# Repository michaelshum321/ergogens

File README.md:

# Ergogen stuff

## [sofle-clone (but it's actually bad)] (sofle-clone/README.md)
My first time playing with ergogen! and my first time in the DIY Keeb space :)

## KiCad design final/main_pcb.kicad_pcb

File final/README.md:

Things changed here:
* made very right edge cut slightly more to the right to account for 0.3mm gap as defined by JLCPCB
* made connecting top right edge stretch slightly more to reach new right edge position
* same with the other side of the right edge

Things did:
Front: horizontal traces
Back: vertical traces

Except for the MCU, which was a bit of a cluster fuck

Change TRRS Power to RAW since it needs to power the other board. oops!

GNDs between the two MCU footpirnts couldn't connect under the footprint, so GND at the top left had to reach around to do it. oops!

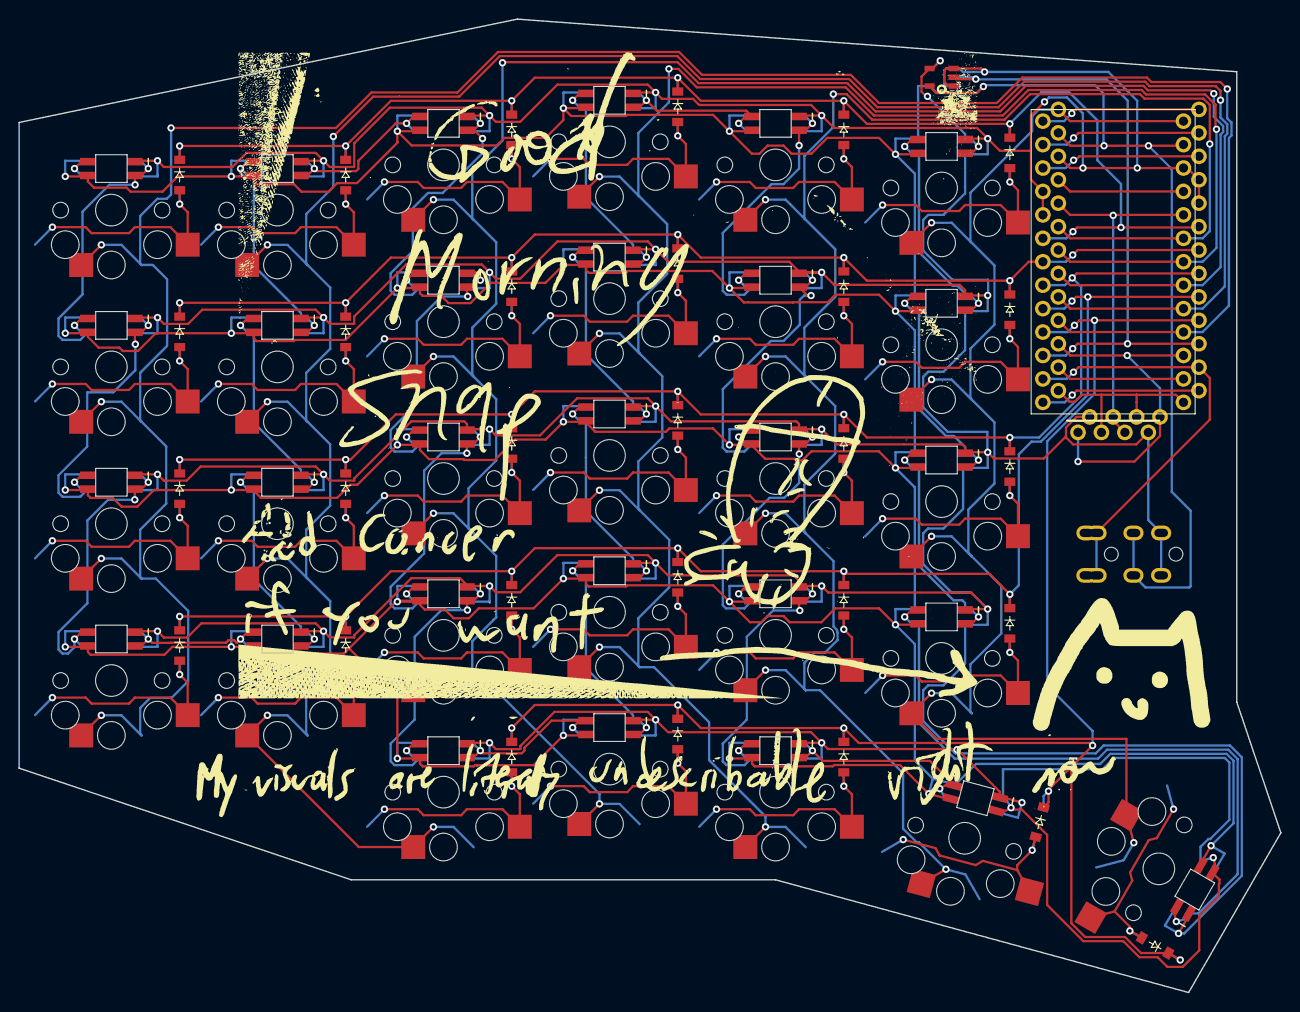
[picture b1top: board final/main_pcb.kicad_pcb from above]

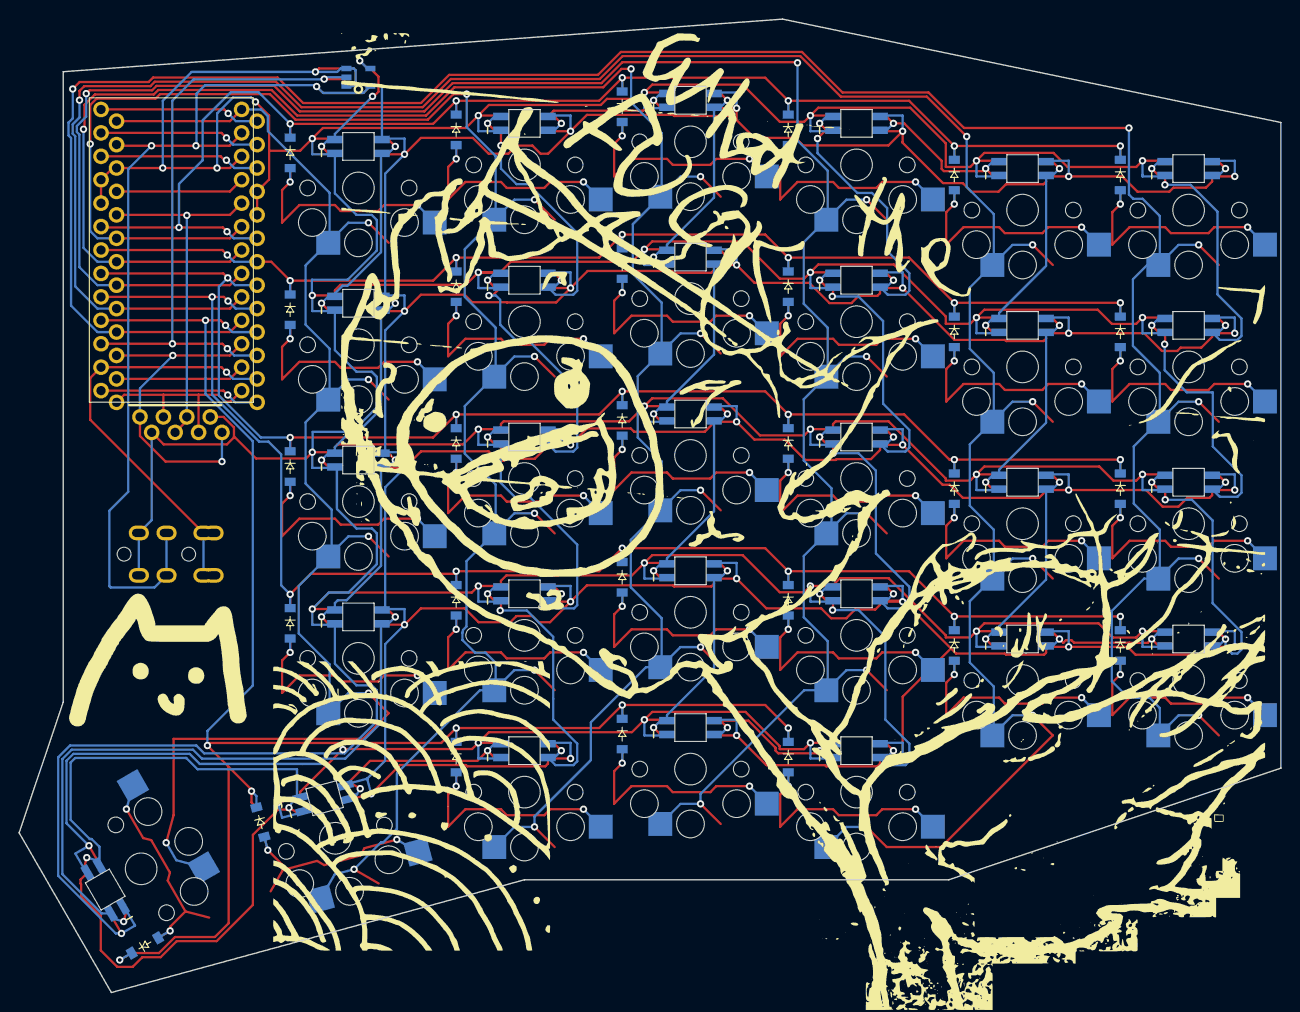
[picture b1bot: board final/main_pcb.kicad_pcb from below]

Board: 2 copper layers, 136.8 x 105.5 mm, 94 parts (31 on the bottom side), 82 nets.

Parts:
 : LOGO; plantjohnny_100
D1, D2, D3, D4, D5, D6, D7, D8, D9, D10, D11, D12, D13, D14, D15, D16, D17, D18, D19, D20, D21, D22, D23, D24, D25, D26, D27, D28, D29: ComboDiode
MCU-AX1, MCU-AX2: ProMicroAX
OLED1, OLED2: OLED
S1, S2, S3, S4, S5, S6, S7, S8, S9, S10, S11, S12, S13, S14, S15, S16, S17, S18, S19, S20, S21, S22, S23, S24, S25, S26, S27, S28, S29: PG1350
TRRS1: TRRS-PJ-320A-dual
_1, _2, _3, _4, _5, _6, _7, _8, _9, _10, _11, _12, _13, _14, _15, _16, _17, _18, _19, _20, _21, _22, _23, _24, _25, _26, _27, _28, _29: SK6812-MINI-E; sk6812-mini-e
_30: 74AHCT1G125

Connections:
3V3: MCU-AX1.VDD, MCU-AX2.VDD, OLED1.VCC, OLED2.VCC
CIndex: MCU-AX1.P29, MCU-AX2.P29, S20.1, S21.1, S22.1, S23.1, S28.1
CInner: MCU-AX1.P11, MCU-AX2.P11, S24.1, S25.1, S26.1, S27.1, S29.1
CMid: MCU-AX1.P28, MCU-AX2.P28, S15.1, S16.1, S17.1, S18.1, S19.1
COuter: MCU-AX1.P22, MCU-AX2.P22, S1.1, S2.1, S3.1, S4.1
CPinky: MCU-AX1.P26, MCU-AX2.P26, S5.1, S6.1, S7.1, S8.1, S9.1
CRing: MCU-AX1.P27, MCU-AX2.P27, S10.1, S11.1, S12.1, S13.1, S14.1
GND: MCU-AX1.GND, MCU-AX2.GND, OLED1.GND, OLED2.GND, TRRS1.4, _1.GND, _2.GND, _3.GND, _4.GND, _5.GND, _6.GND, _7.GND, _8.GND, _9.GND, _10.GND, _11.GND, _12.GND, _13.GND, _14.GND, _15.GND, _16.GND, _17.GND, _18.GND, _19.GND, _20.GND, _21.GND, _22.GND, _23.GND, _24.GND, _25.GND, _26.GND, _27.GND, _28.GND, _29.GND, _30.GND
LED_1: _26.DIN, _27.DOUT
LED_2: _25.DIN, _26.DOUT
LED_3: _24.DIN, _25.DOUT
LED_4: _24.DOUT, _29.DIN
LED_5: _28.DIN, _29.DOUT
LED_6: _19.DIN, _28.DOUT
LED_7: _19.DOUT, _20.DIN
LED_8: _20.DOUT, _21.DIN
LED_9: _21.DOUT, _22.DIN
LED_10: _22.DOUT, _23.DIN
LED_11: _18.DIN, _23.DOUT
LED_12: _17.DIN, _18.DOUT
LED_13: _16.DIN, _17.DOUT
LED_14: _15.DIN, _16.DOUT
LED_15: _14.DIN, _15.DOUT
LED_16: _9.DIN, _14.DOUT
LED_17: _9.DOUT, _10.DIN
LED_18: _10.DOUT, _11.DIN
LED_19: _11.DOUT, _12.DIN
LED_20: _12.DOUT, _13.DIN
LED_21: _8.DIN, _13.DOUT
LED_22: _7.DIN, _8.DOUT
LED_23: _6.DIN, _7.DOUT
LED_24: _5.DIN, _6.DOUT
LED_25: _1.DIN, _5.DOUT
LED_26: _1.DOUT, _2.DIN
LED_27: _2.DOUT, _3.DIN
LED_28: _3.DOUT, _4.DIN
LED_START_3V3: MCU-AX1.P7, MCU-AX2.P7, _30.DIN
LED_START_5V: _27.DIN, _30.DOUT
OLED_SCL: MCU-AX1.P21, MCU-AX2.P21, OLED1.SCL, OLED2.SCL
OLED_SDA: MCU-AX1.P20, MCU-AX2.P20, OLED1.SDA, OLED2.SDA
P0: MCU-AX1.P0, MCU-AX2.P0
P1: MCU-AX1.P1, MCU-AX2.P1
P9: MCU-AX1.P9, MCU-AX2.P9
P10: MCU-AX1.P10, MCU-AX2.P10
P23: MCU-AX1.P23, MCU-AX2.P23
RAW: MCU-AX1.RAW, MCU-AX2.RAW, TRRS1.3, _1.VDD, _2.VDD, _3.VDD, _4.VDD, _5.VDD, _6.VDD, _7.VDD, _8.VDD, _9.VDD, _10.VDD, _11.VDD, _12.VDD, _13.VDD, _14.VDD, _15.VDD, _16.VDD, _17.VDD, _18.VDD, _19.VDD, _20.VDD, _21.VDD, _22.VDD, _23.VDD, _24.VDD, _25.VDD, _26.VDD, _27.VDD, _28.VDD, _29.VDD, _30.VCC
RBottom: D1.2, D5.2, D10.2, D15.2, D20.2, D24.2, MCU-AX1.P5, MCU-AX2.P5
RHome: D2.2, D6.2, D11.2, D16.2, D21.2, D25.2, MCU-AX1.P4, MCU-AX2.P4
RMod: D9.2, D14.2, D19.2, D28.2, D29.2, MCU-AX1.P6, MCU-AX2.P6
RNum: D4.2, D8.2, D13.2, D18.2, D23.2, D27.2, MCU-AX1.P2, MCU-AX2.P2
RST: MCU-AX1.RST, MCU-AX2.RST
RTop: D3.2, D7.2, D12.2, D17.2, D22.2, D26.2, MCU-AX1.P3, MCU-AX2.P3
TRS_DATA: MCU-AX1.P8, MCU-AX2.P8, TRRS1.1, TRRS1.2
index_bottom: D20.1, S20.2
index_home: D21.1, S21.2
index_mod: D19.1, S19.2
index_num: D23.1, S23.2
index_top: D22.1, S22.2
inner_bottom: D24.1, S24.2
inner_home: D25.1, S25.2
inner_num: D27.1, S27.2
inner_top: D26.1, S26.2
layer_cluster: D28.1, S28.2
middle_bottom: D15.1, S15.2
middle_home: D16.1, S16.2
middle_mod: D14.1, S14.2
middle_num: D18.1, S18.2
middle_top: D17.1, S17.2
outer_bottom: D1.1, S1.2
outer_home: D2.1, S2.2
outer_num: D4.1, S4.2
outer_top: D3.1, S3.2
pinky_bottom: D5.1, S5.2
pinky_home: D6.1, S6.2
pinky_num: D8.1, S8.2
pinky_top: D7.1, S7.2
ring_bottom: D10.1, S10.2
ring_home: D11.1, S11.2
ring_mod: D9.1, S9.2
ring_num: D13.1, S13.2
ring_top: D12.1, S12.2
space_cluster: D29.1, S29.2

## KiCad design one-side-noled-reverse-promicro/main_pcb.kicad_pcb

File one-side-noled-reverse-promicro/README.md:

The Pro Micros are wired up so that the two footprints are all connected on the Front, except for 1 via closest to one side's pin.

This way, there is more space to have vias in the middle of the ProMicro for other important things

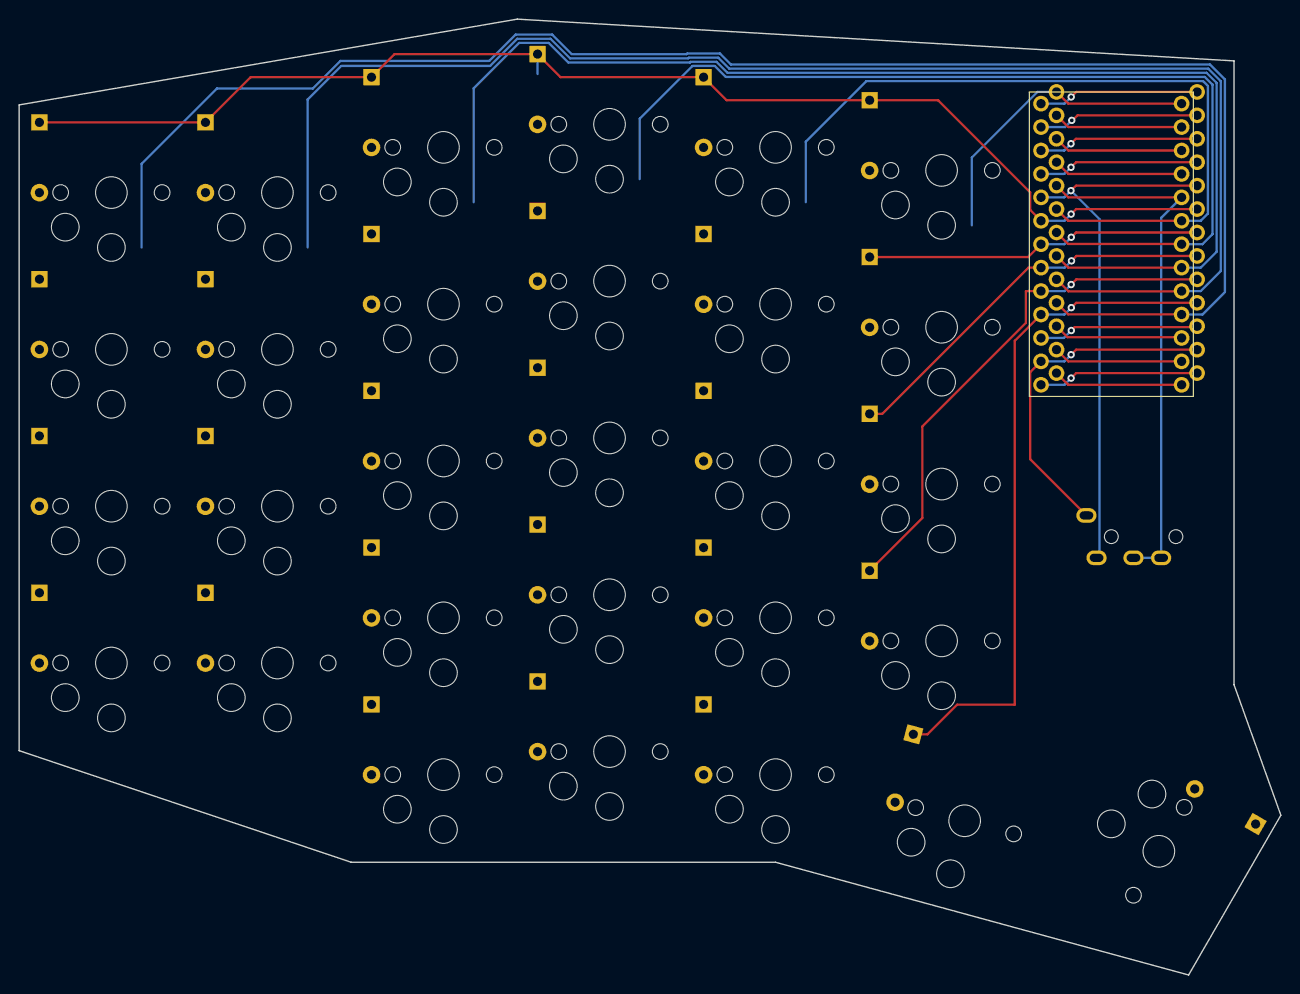
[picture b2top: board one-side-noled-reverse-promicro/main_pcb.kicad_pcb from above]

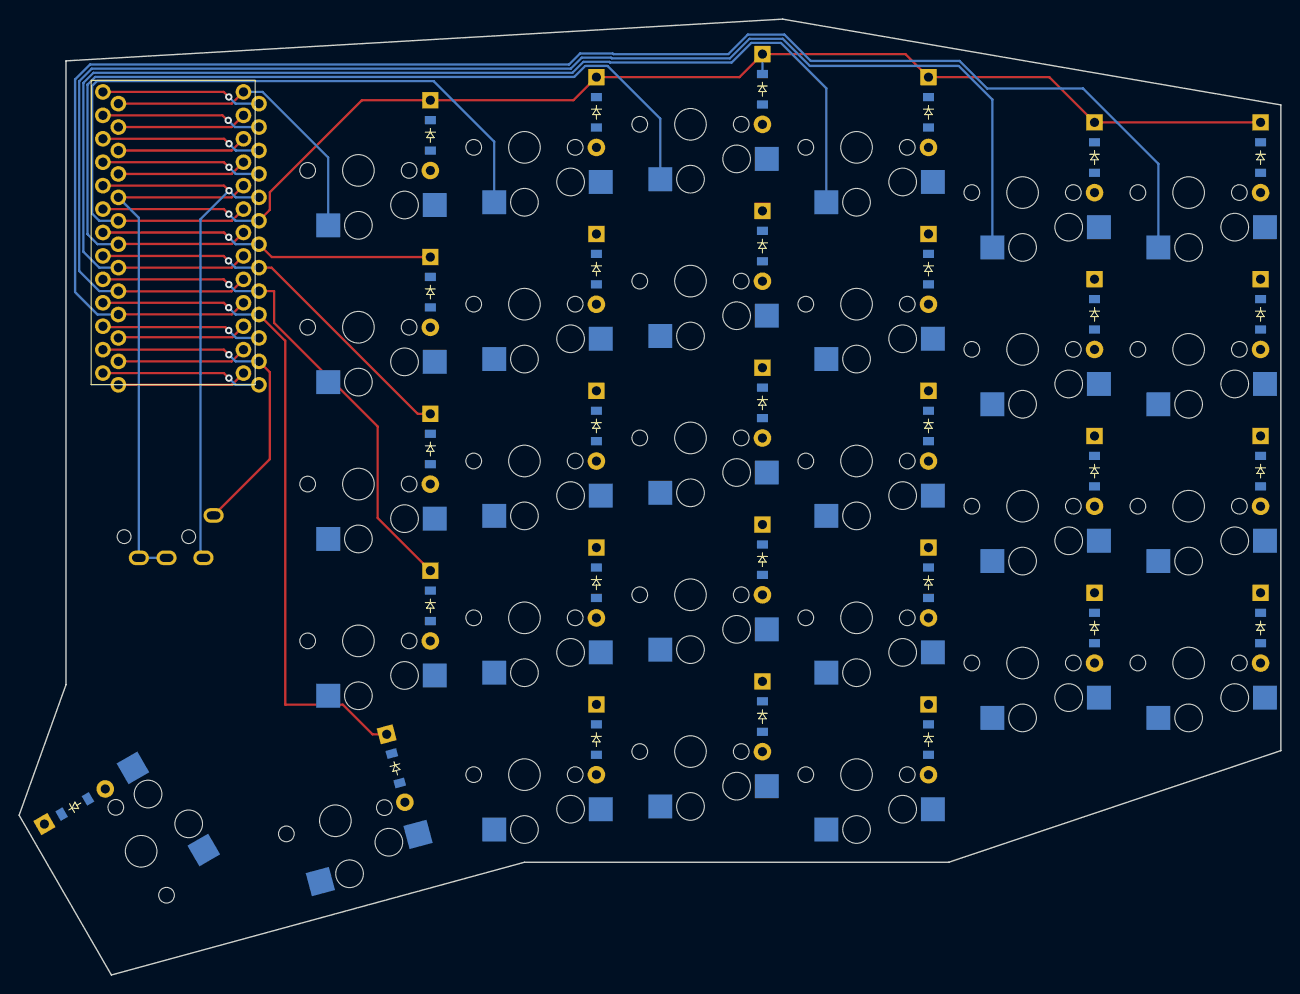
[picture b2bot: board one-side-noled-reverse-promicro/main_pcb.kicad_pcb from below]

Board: 2 copper layers, 136.8 x 103.6 mm, 61 parts (30 on the bottom side), 53 nets.

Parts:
D1, D2, D3, D4, D5, D6, D7, D8, D9, D10, D11, D12, D13, D14, D15, D16, D17, D18, D19, D20, D21, D22, D23, D24, D25, D26, D27, D28, D29: ComboDiode
MCU-AX1, MCU-AX2: ProMicroAX
S1, S2, S3, S4, S5, S6, S7, S8, S9, S10, S11, S12, S13, S14, S15, S16, S17, S18, S19, S20, S21, S22, S23, S24, S25, S26, S27, S28, S29: PG1350
TRRS1: TRRS-PJ-320A-dual

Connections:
GND: MCU-AX1.GND, MCU-AX2.GND, TRRS1.2
P0: MCU-AX1.P0, MCU-AX2.P0
P1: MCU-AX1.P1, MCU-AX2.P1
P2: D4.1, D8.1, D13.1, D18.1, D23.1, D27.1, MCU-AX1.P2, MCU-AX2.P2
P3: D3.1, D7.1, D12.1, D17.1, D22.1, D26.1, MCU-AX1.P3, MCU-AX2.P3
P4: D2.1, D6.1, D11.1, D16.1, D21.1, D25.1, MCU-AX1.P4, MCU-AX2.P4
P5: D1.1, D5.1, D10.1, D15.1, D20.1, D24.1, MCU-AX1.P5, MCU-AX2.P5
P6: D9.1, D14.1, D19.1, D28.1, D29.1, MCU-AX1.P6, MCU-AX2.P6
P7: MCU-AX1.P7, MCU-AX2.P7
P8: MCU-AX1.P8, MCU-AX2.P8, TRRS1.1
P9: MCU-AX1.P9, MCU-AX2.P9
P10: MCU-AX1.P10, MCU-AX2.P10
P11: MCU-AX1.P11, MCU-AX2.P11, S24.1, S25.1, S26.1, S27.1, S29.1
P20: MCU-AX1.P20, MCU-AX2.P20
P21: MCU-AX1.P21, MCU-AX2.P21
P22: MCU-AX1.P22, MCU-AX2.P22, S1.1, S2.1, S3.1, S4.1
P23: MCU-AX1.P23, MCU-AX2.P23
P26: MCU-AX1.P26, MCU-AX2.P26, S5.1, S6.1, S7.1, S8.1, S9.1
P27: MCU-AX1.P27, MCU-AX2.P27, S10.1, S11.1, S12.1, S13.1, S14.1
P28: MCU-AX1.P28, MCU-AX2.P28, S15.1, S16.1, S17.1, S18.1, S19.1
P29: MCU-AX1.P29, MCU-AX2.P29, S20.1, S21.1, S22.1, S23.1, S28.1
RAW: MCU-AX1.RAW, MCU-AX2.RAW
RST: MCU-AX1.RST, MCU-AX2.RST
VDD: MCU-AX1.VDD, MCU-AX2.VDD, TRRS1.3, TRRS1.4
index_bottom: D20.2, S20.2
index_home: D21.2, S21.2
index_mod: D19.2, S19.2
index_num: D23.2, S23.2
index_top: D22.2, S22.2
inner_bottom: D24.2, S24.2
inner_home: D25.2, S25.2
inner_num: D27.2, S27.2
inner_top: D26.2, S26.2
layer_cluster: D28.2, S28.2
middle_bottom: D15.2, S15.2
middle_home: D16.2, S16.2
middle_mod: D14.2, S14.2
middle_num: D18.2, S18.2
middle_top: D17.2, S17.2
outer_bottom: D1.2, S1.2
outer_home: D2.2, S2.2
outer_num: D4.2, S4.2
outer_top: D3.2, S3.2
pinky_bottom: D5.2, S5.2
pinky_home: D6.2, S6.2
pinky_num: D8.2, S8.2
pinky_top: D7.2, S7.2
ring_bottom: D10.2, S10.2
ring_home: D11.2, S11.2
ring_mod: D9.2, S9.2
ring_num: D13.2, S13.2
ring_top: D12.2, S12.2
space_cluster: D29.2, S29.2

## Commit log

2023-09-16 Part 1 Points done
2023-09-17 clone board for sofle
2023-09-17 sofle outline clone done
2023-09-17 pcb diode hotswaps and promicro are placed
2023-09-17 add oled
2023-09-23 Add button rough, where should OLED go?
2023-09-23 Wire Keyboard matrix to Pro Micro (Finish part 3)
2023-09-23 Add ergogen npm pkg
2023-09-25 Move things around for custom footprints arrange OLED, RESET, TRRS
2023-09-26 Add default LED footprint, put in placeholder position Move diode to new spot Flip Footprint so LED is on top, hotswap socket on bottom
2023-09-26 LEDs are wired up!!
2023-09-30 Add build open script
2023-09-30 Add diode, LED from corney-island. Use new components in config
2023-09-30 Add Reversible Diode
2023-09-30 Add reversible LED
2023-09-30 add Reverse on Choc Hotswap
2023-09-30 Flip Diode so signal in is on top for each row shift diode into position to the right of LED
2023-09-30 Add README
2023-10-02 Add Combo Display for OLED from CorneyIsland
2023-10-02 Make ProMicro Footprint - holes sizes and diameters are copied from 0xB2 Pro Micro Clone
2023-10-02 Remove Reset button Add Reverse Symmetric TRRS for Serial 1 cable cnx Change OLED to combo-display to include Jumpers for reversible
2023-10-03 Rearrange ProMicroAX Footprint
2023-10-03 remove rotation on bottom pins
2023-10-03 Add super cool ProMicro AX footprint Change VCC to RAW
2023-10-04 Add footprint that's just flipped Change ergo footprint to allow being on the back
2023-10-04 Remove bottom pins from ergo footprint to make it reversible Set reversed footprint in config to have offset
2023-10-05 Use correct AX pins for PCB
2023-10-05 Add docs
2023-10-06 make it even more dumb
2023-10-06 Fix Thumb row
2023-10-08 remove bad PCBs
2023-10-08 Include THT for back/front shift promicro so there's more space move around TRRS so it wires up better Add basic routed PCB
2023-10-08 Add Reversible Pro Micros
2023-10-08 Add back reversible TRRS
2023-10-08 Use Variable for MCU Offset
2023-10-09 Change Diode to use Vias Move cmts of MCU offsets to units
2023-10-09 add back reversible LED x_x
2023-10-09 Add back OLED w/ WIP Positioning Add Choc Wired, add Routing + Via Shorthand, Use it
2023-10-11 Cleanup choc wired Use CorneyIsland's new RGB
2023-10-13 Add OLED kicad footprint, front and back Add ergogen footprint for OLED
2023-10-13 Add nets for OLED
2023-10-13 Fix OLED side err Position OLED on Keeb finally
2023-10-13 fix net on choc wired Add wired sk6812-mini-e footprint
2023-10-13 Add Kicad v7 Blank Project
2023-10-13 Change VDD to 3V3
2023-10-13 Add meaningful Nets to MCU Use Nets for OLED Header
2023-10-13 Use meaningful nets everywhere
2023-10-13 Fix rotation on solder pads for Choc Wire and LED
2023-10-14 Move v7 and v5 footprints into different folders Add LogicShifter ergo Add playground PCB files
2023-10-14 Fix rounding on rotated RGB Fix Traces on Choc Add Logic Shifter w/ backside hole on wrong side lol
2023-10-15 i think im done
2023-10-15 Fix outline to have 0.3mm gap to traces
2023-10-15 Update Gerbers to have newest and improved gap to outline of board
2023-10-17 Add picture footprnts and add to PCB Fix TRRS Power line on kicadpcb to 5v Add Readme on changes made
